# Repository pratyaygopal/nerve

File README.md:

# nerve
Code for our ECE395 Project

<br>
<br>
<br>
</td>

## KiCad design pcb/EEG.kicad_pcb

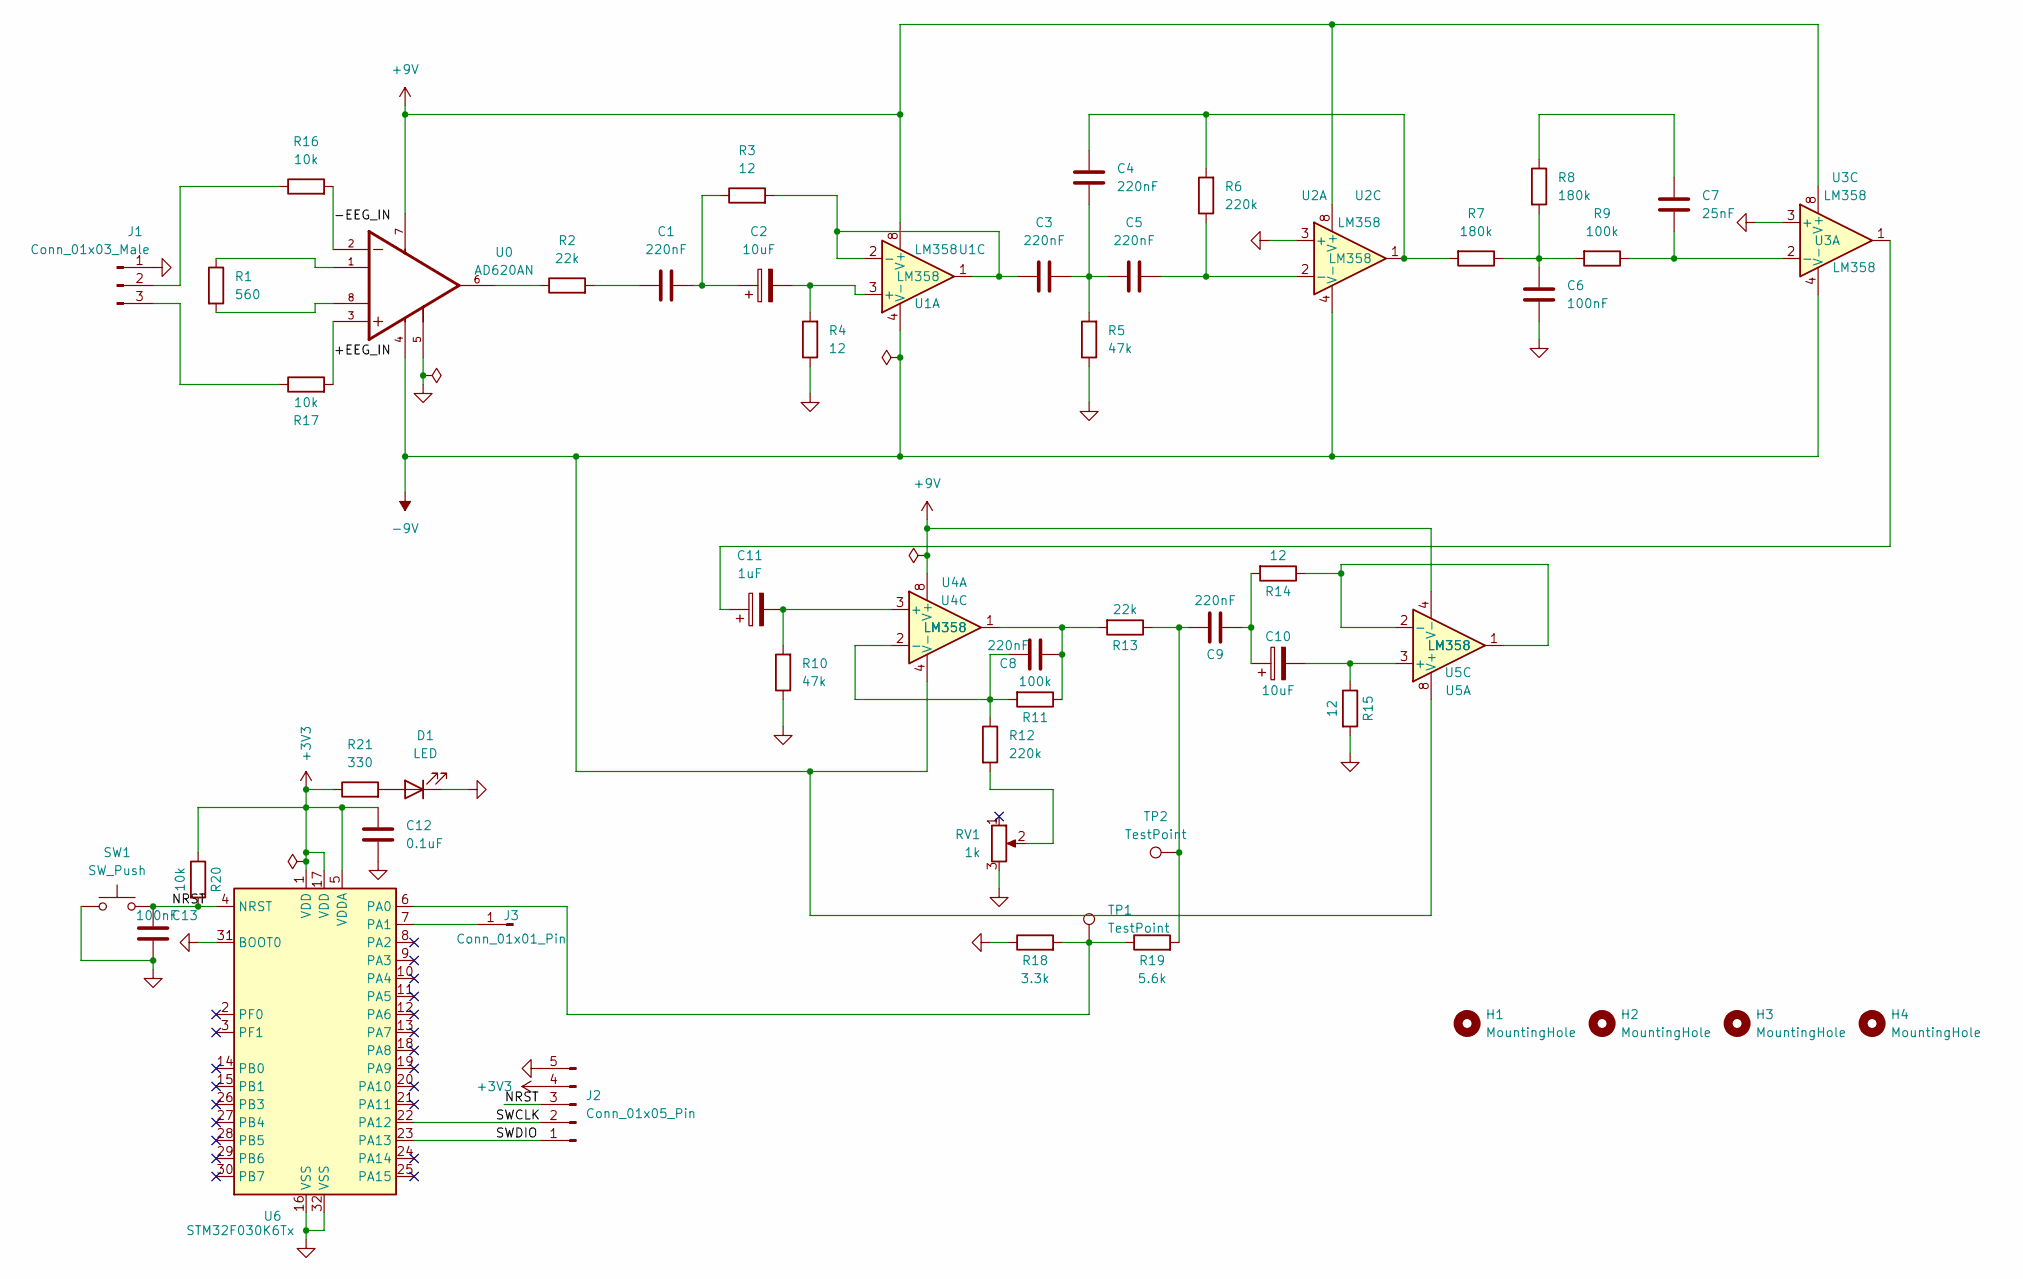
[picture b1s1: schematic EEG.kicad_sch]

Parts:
C1, C3, C4, C5, C8, C9: 220nF; C_0201_0603Metric
C2: 10uF; CP_EIA-3216-10_Kemet-I
C6, C13: 100nF; C_0201_0603Metric
C7: 25nF; C_0201_0603Metric
C10: 10uF; C_0201_0603Metric
C11: 1uF; CP_EIA-3216-10_Kemet-I
C12: 0.1uF; C_0201_0603Metric
D1: LED; LED_0603_1608Metric
H1, H2, H3, H4: MountingHole; MountingHole_2.2mm_M2
J1: Conn_01x03_Male; FanPinHeader_1x03_P2.54mm_Vertical
J2: Conn_01x05_Pin; JST_PH_S5B-PH-K_1x05_P2.00mm_Horizontal
J3: Conn_01x01_Pin; PinHeader_1x01_P1.00mm_Horizontal
R1: 560; R_0805_2012Metric
R2, R13: 22k; R_0805_2012Metric
R3, R4, R14, R15: 12; R_0805_2012Metric
R5, R10: 47k; R_0805_2012Metric
R6, R12: 220k; R_0805_2012Metric
R7, R8: 180k; R_0805_2012Metric
R9, R11: 100k; R_0805_2012Metric
R16, R17, R20: 10k; R_0805_2012Metric
R18: 3.3k; R_0805_2012Metric
R19: 5.6k; R_0805_2012Metric
R21: 330; R_0805_2012Metric
RV1: 1k; Potentiometer_Bourns_3269W_Vertical
SW1: SW_Push; SW_PUSH_6mm
TP1, TP2: TestPoint; TestPoint_THTPad_1.0x1.0mm_Drill0.5mm
U0: AD620AN; DIP787W46P254L1016H533Q8; PARTREV H
U1, U2, U3, U4, U5: LM358; DIP-8_W7.62mm
U6: STM32F030K6Tx; LQFP-32_7x7mm_P0.8mm

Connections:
+3V3: C12.1, J2.4, R20.1, R21.1, U6.1 (VDD), U6.5 (VDDA), U6.17 (VDD)
+9V: U0.7, U1.8 (V+), U2.8 (V+), U3.8 (V+), U4.8 (V+), U5.4 (V-)
-9V: U0.4, U1.4 (V-), U2.4 (V-), U3.4 (V-), U4.4 (V-), U5.8 (V+)
/+EEG_IN: R17.2, U0.3
/-EEG_IN: R16.2, U0.2
/NRST: C13.1, J2.3, R20.2, SW1.2, U6.4 (NRST)
/SWCLK: J2.2, U6.22 (PA12)
/SWDIO: J2.1, U6.23 (PA13)
GND: C6.1, C12.2, C13.2, D1.1 (K), J1.1, J2.5, R4.1, R5.1, R10.1, R15.2, R18.1, RV1.3, SW1.1, U0.5, U2.3 (+), U3.3 (+), U6.16 (VSS), U6.31 (BOOT0), U6.32 (VSS)
unnamed: C1.1, R2.2
unnamed: C1.2, C2.1, R3.1
unnamed: C3.2, C4.1, C5.1, R5.2
unnamed: C4.2, R6.2, R7.2, U2.1
unnamed: C6.2, R7.1, R8.2, R9.2
unnamed: C7.2, R8.1
unnamed: C8.2, R11.1, R13.2, U4.1
unnamed: C9.1, R13.1, R19.2, TP2.1
unnamed: C9.2, C10.1, R14.2
unnamed: C11.1, U3.1
unnamed: D1.2 (A), R21.2
unnamed: J1.2, R16.1
unnamed: J1.3, R17.1
unnamed: J3.1, U6.7 (PA1)
unnamed: R1.1, U0.1
unnamed: R1.2, U0.8
unnamed: R2.1, U0.6
unnamed: R12.2, RV1.2
unnamed: C2.2, R4.2, U1.3 (+)
unnamed: C3.1, R3.2, U1.1, U1.2 (-)
unnamed: C5.2, R6.1, U2.2 (-)
unnamed: C7.1, R9.1, U3.2 (-)
unnamed: C11.2, R10.2, U4.3 (+)
unnamed: C8.1, R11.2, R12.1, U4.2 (-)
unnamed: C10.2, R15.1, U5.3 (+)
unnamed: R14.1, U5.1, U5.2 (-)
unnamed: R18.2, R19.1, TP1.1, U6.6 (PA0)

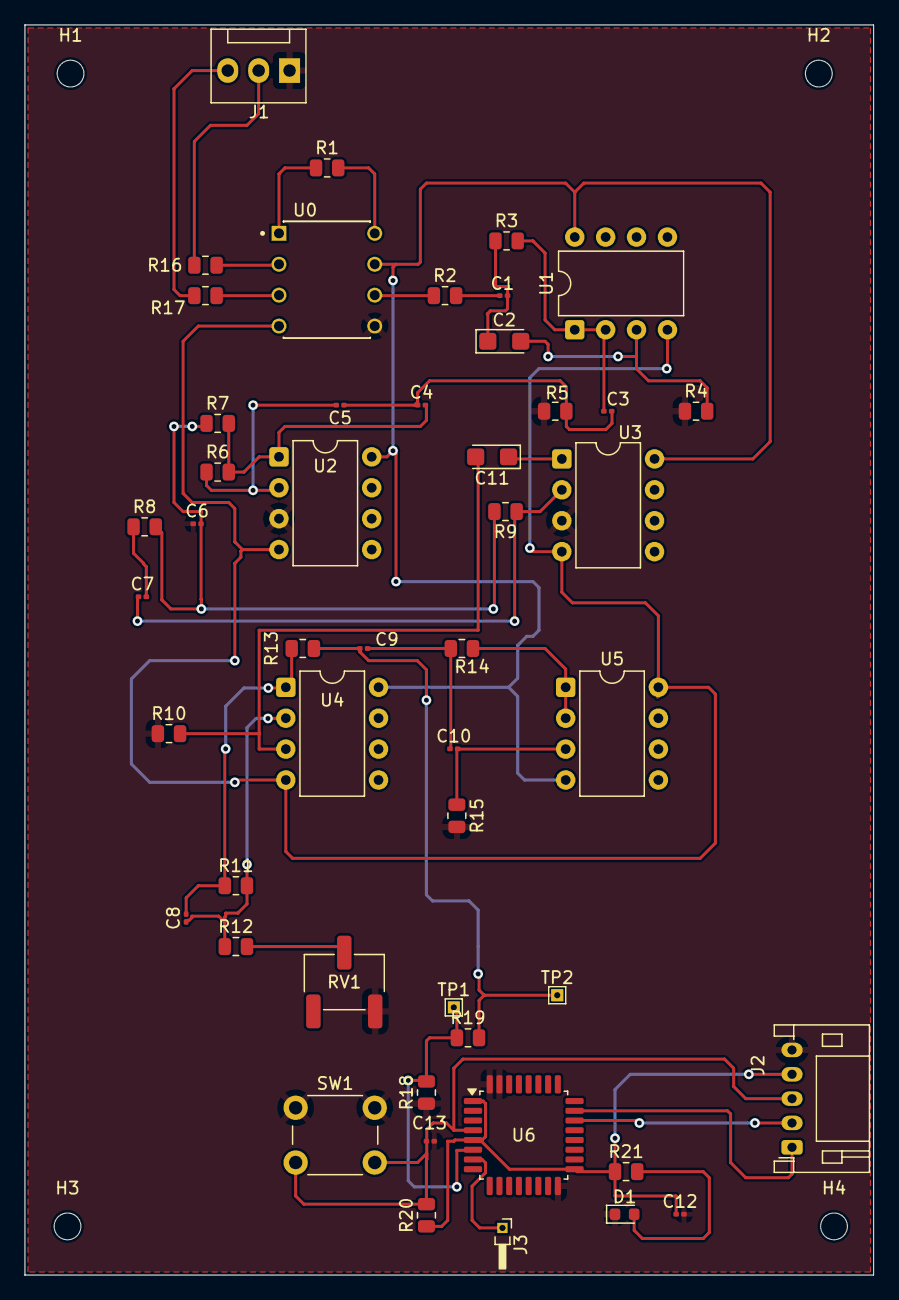
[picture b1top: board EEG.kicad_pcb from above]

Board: 2 copper layers, 69.8 x 102.8 mm, 53 parts (0 on the bottom side), 36 nets.

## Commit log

2025-12-15 image commit
2025-12-15 image update
